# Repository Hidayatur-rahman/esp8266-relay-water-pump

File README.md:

# ESP8266 Relay – Water Pump Controller

A compact mains-powered ESP8266 (ESP-12E) board with a 5V relay, designed to switch a water pump (or any AC load) over Wi-Fi. Works well with ESPHome / Home Assistant.

**Board:** 2-layer PCB, ~65 × 62 mm  
**Design tool:** KiCad 10  
**Revision:** 1.0 (2026-10-16)

> ⚠️ **WARNING – MAINS VOLTAGE**  
> This board connects directly to AC mains. Only build and test it if you know how to work safely with high voltage. Always disconnect power before touching the board, use a properly rated fuse, and connect the Earth terminal. Use at your own risk.

## Features

- ESP-12E (ESP8266) Wi-Fi module
- On-board AC-DC converter (HLK-PM01, 5V) – no external adapter needed
- AMS1117-3.3 regulator for the ESP8266
- SRD-05VDC-SL-C relay (SPDT; board uses COM and NO contacts)
- Optocoupler (EL817) isolating the ESP8266 from the relay driver
- Relay status LED
- SMD fuse on the switched AC output
- Screw terminals for AC input and AC output (with Earth)
- Header for I2C sensors, UART/TTL programming header
- Reset and Flash buttons, plus a connector for an external push button
- Isolation slots in the PCB between the high-voltage and low-voltage areas

## Block Diagram

```
AC IN ──► HLK-PM01 (5V) ──► AMS1117 (3.3V) ──► ESP-12E
  │              │                                  │ GPIO13
  │              └──► Relay coil ◄── S8050 ◄── EL817 ◄┘
  │
  └──► Relay COM ──► NO ──► Fuse ──► AC OUT (pump)
```

## Pin Mapping

| ESP8266 Pin | Function |
|---|---|
| GPIO13 | Relay control (via 330R → EL817 optocoupler → S8050) |
| GPIO12 | External push button (J5, to GND) |
| GPIO4 | I2C SDA (J4, 4.7k pull-up) |
| GPIO5 | I2C SCL (J4, 4.7k pull-up) |
| GPIO0 | Flash button (SW2), 10k pull-up |
| GPIO2 | 10k pull-up |
| GPIO15 | 10k pull-down |
| GPIO1 / GPIO3 | TX / RX on TTL header (J2) |
| RST | Reset button (SW1), 10k pull-up |
| EN | 10k pull-up |

GPIO12 has no external pull-up, so enable the internal pull-up in firmware.

## Connectors

| Ref | Name | Description |
|---|---|---|
| J3 | AC IN | Mains input: L, Earth, N |
| J1 | AC OUT | Switched output: N, Earth, L (through relay and fuse) |
| J2 | TTL | 3.3V, GND, RX, TX, RST (for flashing) |
| J4 | I2C | 3.3V, GND, SCL, SDA |
| J5 | Push Button | GPIO12 and GND |

## Main Components

| Ref | Part |
|---|---|
| U1 | ESP-12E |
| U2 | EL817 optocoupler |
| U3 | HLK-PM01 (AC-DC 5V, 3W) |
| U4 | AMS1117-3.3 |
| K1 | SRD-05VDC-SL-C relay |
| Q1 | S8050 NPN transistor |
| D1 | Flyback diode (SMA) |
| D2 + R11 | Relay status LED + 330R resistor |
| F1 | SMD fuse, 2010 (5025 metric) – choose a rating that suits your load |

## Flashing

1. Connect a USB-TTL adapter (3.3V logic) to J2: GND, TX → RX, RX → TX.
2. Hold the **Flash** button (SW2), press **Reset** (SW1), then release Flash.
3. Upload your firmware (ESPHome, Arduino, etc.).

> Power the board from a USB-TTL adapter's 3.3V only while mains is **disconnected**, or power it from the mains side, but never both at once.

## Example ESPHome Config

```yaml
esp8266:
  board: esp01_1m

switch:
  - platform: gpio
    pin: GPIO13
    name: "Water Pump"
    id: water_pump

binary_sensor:
  - platform: gpio
    pin:
      number: GPIO12
      mode: INPUT_PULLUP
      inverted: true
    name: "Pump Button"
    on_press:
      - switch.toggle: water_pump

i2c:
  sda: GPIO4
  scl: GPIO5
```

## Repository Files

- `esp8266-relay-waterpump.kicad_sch` – schematic
- `esp8266-relay-waterpump.kicad_pcb` – PCB layout

Open both files with KiCad 10 or newer.

## License

MIT License

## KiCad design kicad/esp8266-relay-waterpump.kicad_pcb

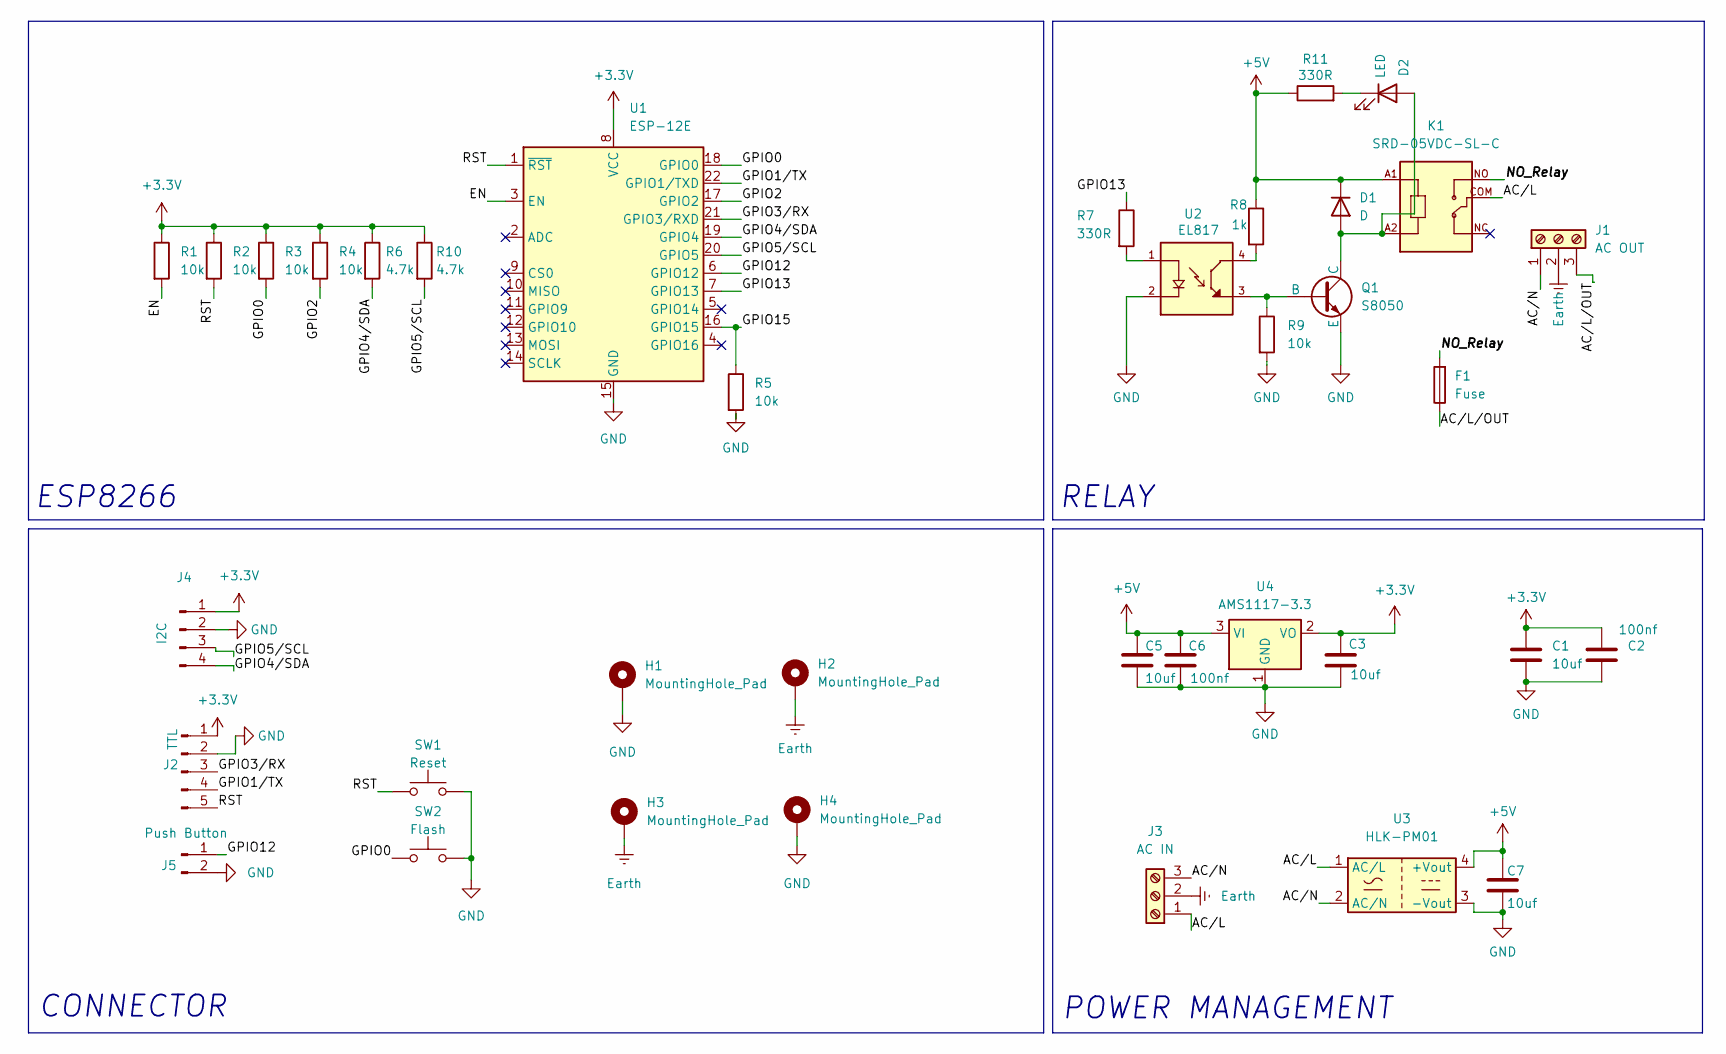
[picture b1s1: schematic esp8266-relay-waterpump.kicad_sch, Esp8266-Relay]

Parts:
C1, C3, C5, C7: 10uf; C_0805_2012Metric
C2, C6: 100nf; C_0603_1608Metric
D1: D; D_SMA
D2: LED; LED_0805_2012Metric_Pad1.15x1.40mm_HandSolder
F1: Fuse; Fuse_2010_5025Metric_Pad1.52x2.65mm_HandSolder
H1, H2, H3, H4: MountingHole_Pad; MountingHole_2.5mm_Pad_Via
J1: AC OUT; Terminal_Block_1x3_5.08mm_Molex
J2: TTL; PinHeader_1x05_P2.00mm_Vertical
J3: AC IN; Terminal_Block_1x3_5.08mm_Molex
J4: I2C; JST_EH_B4B-EH-A_1x04_P2.50mm_Vertical
J5: Push Button; JST_EH_B2B-EH-A_1x02_P2.50mm_Vertical
K1: SRD-05VDC-SL-C; RELAY_SRD-05VDC-SL-C
Q1: S8050; SOT-23
R1, R2, R3, R4, R5, R9: 10k; R_0805_2012Metric_Pad1.20x1.40mm_HandSolder
R6, R10: 4.7k; R_0805_2012Metric_Pad1.20x1.40mm_HandSolder
R7: 330R; R_0805_2012Metric_Pad1.20x1.40mm_HandSolder
R8: 1k; R_0805_2012Metric_Pad1.20x1.40mm_HandSolder
R11: 330R; R_0805_2012Metric
SW1: Reset; SW_SPST_TS-1088-xR020
SW2: Flash; SW_SPST_TS-1088-xR020
U1: ESP-12E
U2: EL817; SOIC254P1030X460-4N; PARTREV 7
U3: HLK-PM01; Converter_ACDC_Hi-Link_HLK-PMxx
U4: AMS1117-3.3; SOT-223-3_TabPin2

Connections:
+3.3V: C1.1, C2.1, C3.1, J2.1, J4.1, R1.1, R2.1, R3.1, R4.1, R6.1, R10.1, U1.8 (VCC), U4.2 (VO)
+5V: C5.1, C6.1, C7.1, D1.1 (K), K1.A1, R8.1, R11.1, U3.4 (+Vout), U4.3 (VI)
/AC/L: J3.1, K1.COM, U3.1 (AC/L)
/AC/L/OUT: F1.1, J1.3
/AC/N: J1.1, J3.3, U3.2 (AC/N)
/EN: R1.2, U1.3 (EN)
/GPIO0: R3.2, SW2.1, U1.18 (GPIO0)
/GPIO1/TX: J2.4, U1.22 (GPIO1/TXD)
/GPIO2: R4.2, U1.17 (GPIO2)
/GPIO3/RX: J2.3, U1.21 (GPIO3/RXD)
/GPIO4/SDA: J4.4, R6.2, U1.19 (GPIO4)
/GPIO5/SCL: J4.3, R10.2, U1.20 (GPIO5)
/GPIO12: J5.1, U1.6 (GPIO12)
/GPIO13: R7.1, U1.7 (GPIO13)
/GPIO15: R5.1, U1.16 (GPIO15)
/NO_Relay: F1.2, K1.NO
/RST: J2.5, R2.2, SW1.1, U1.1 (~RST)
Earth: H2.1 (1_1), H3.1 (1_1), J1.2, J3.2
GND: C1.2, C2.2, C3.2, C5.2, C6.2, C7.2, H1.1 (1_1), H4.1 (1_1), J2.2, J4.2, J5.2, Q1.3 (E), R5.2, R9.2, SW1.2, SW2.2, U1.15 (GND), U2.2, U3.3 (-Vout), U4.1 (GND)
unnamed: D1.2 (A), D2.2 (A), K1.A2, Q1.1 (C)
unnamed: D2.1 (K), R11.2
unnamed: Q1.2 (B), R9.1, U2.3
unnamed: R7.2, U2.1
unnamed: R8.2, U2.4

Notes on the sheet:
CONNECTOR
POWER MANAGEMENT
RELAY
ESP8266

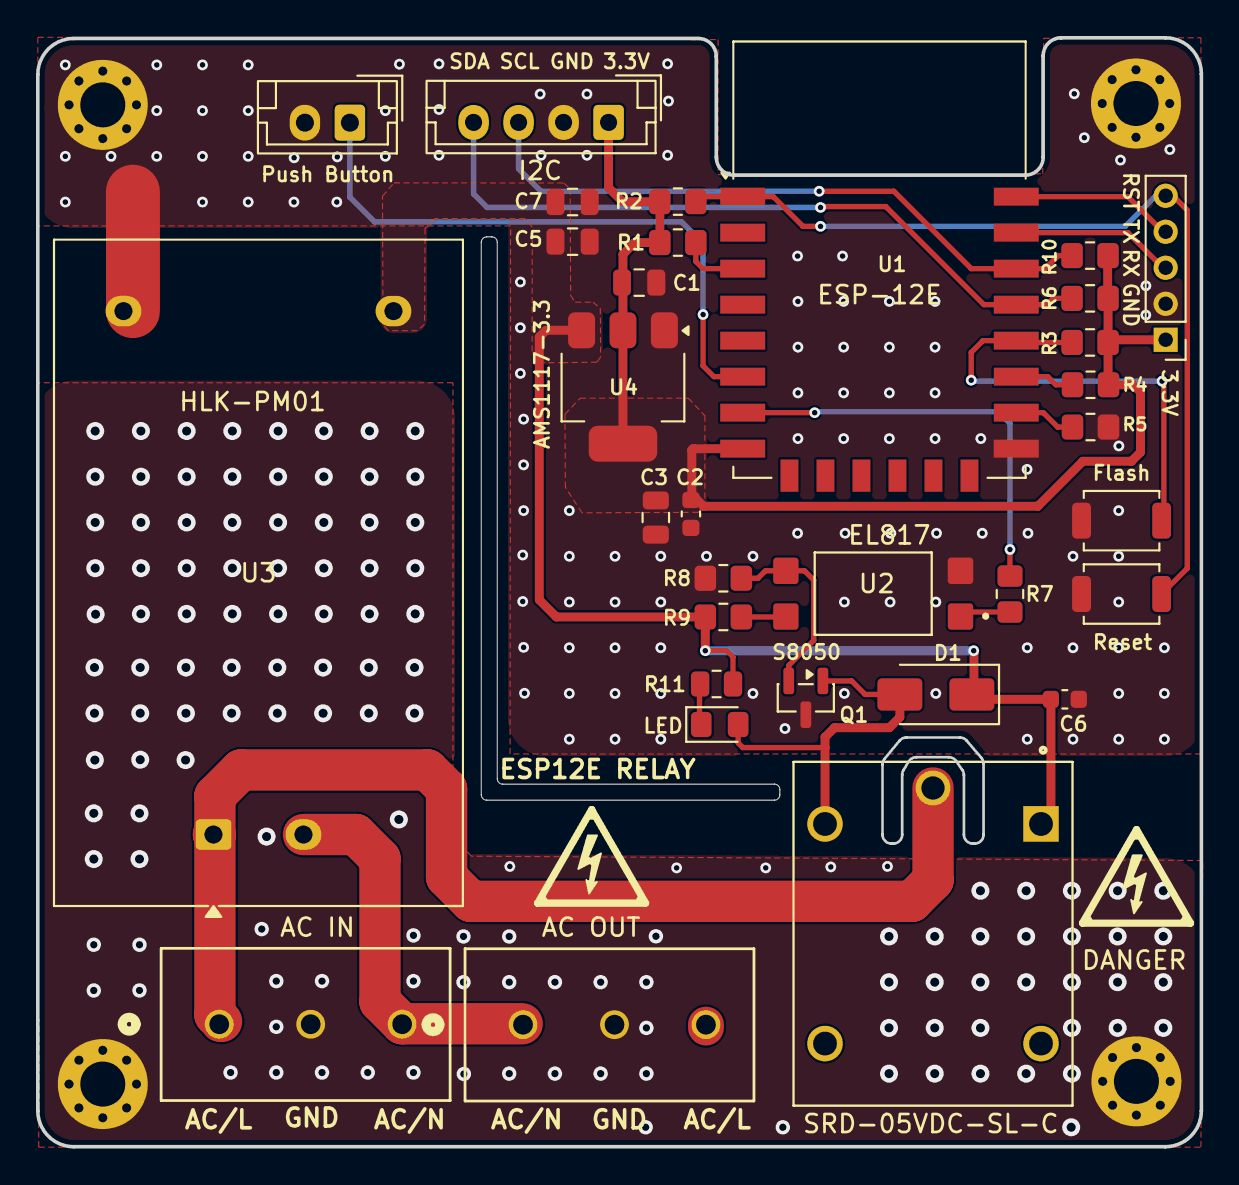
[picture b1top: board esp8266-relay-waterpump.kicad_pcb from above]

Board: 2 copper layers, 64.6 x 61.6 mm, 37 parts (1 on the bottom side), 24 nets.
